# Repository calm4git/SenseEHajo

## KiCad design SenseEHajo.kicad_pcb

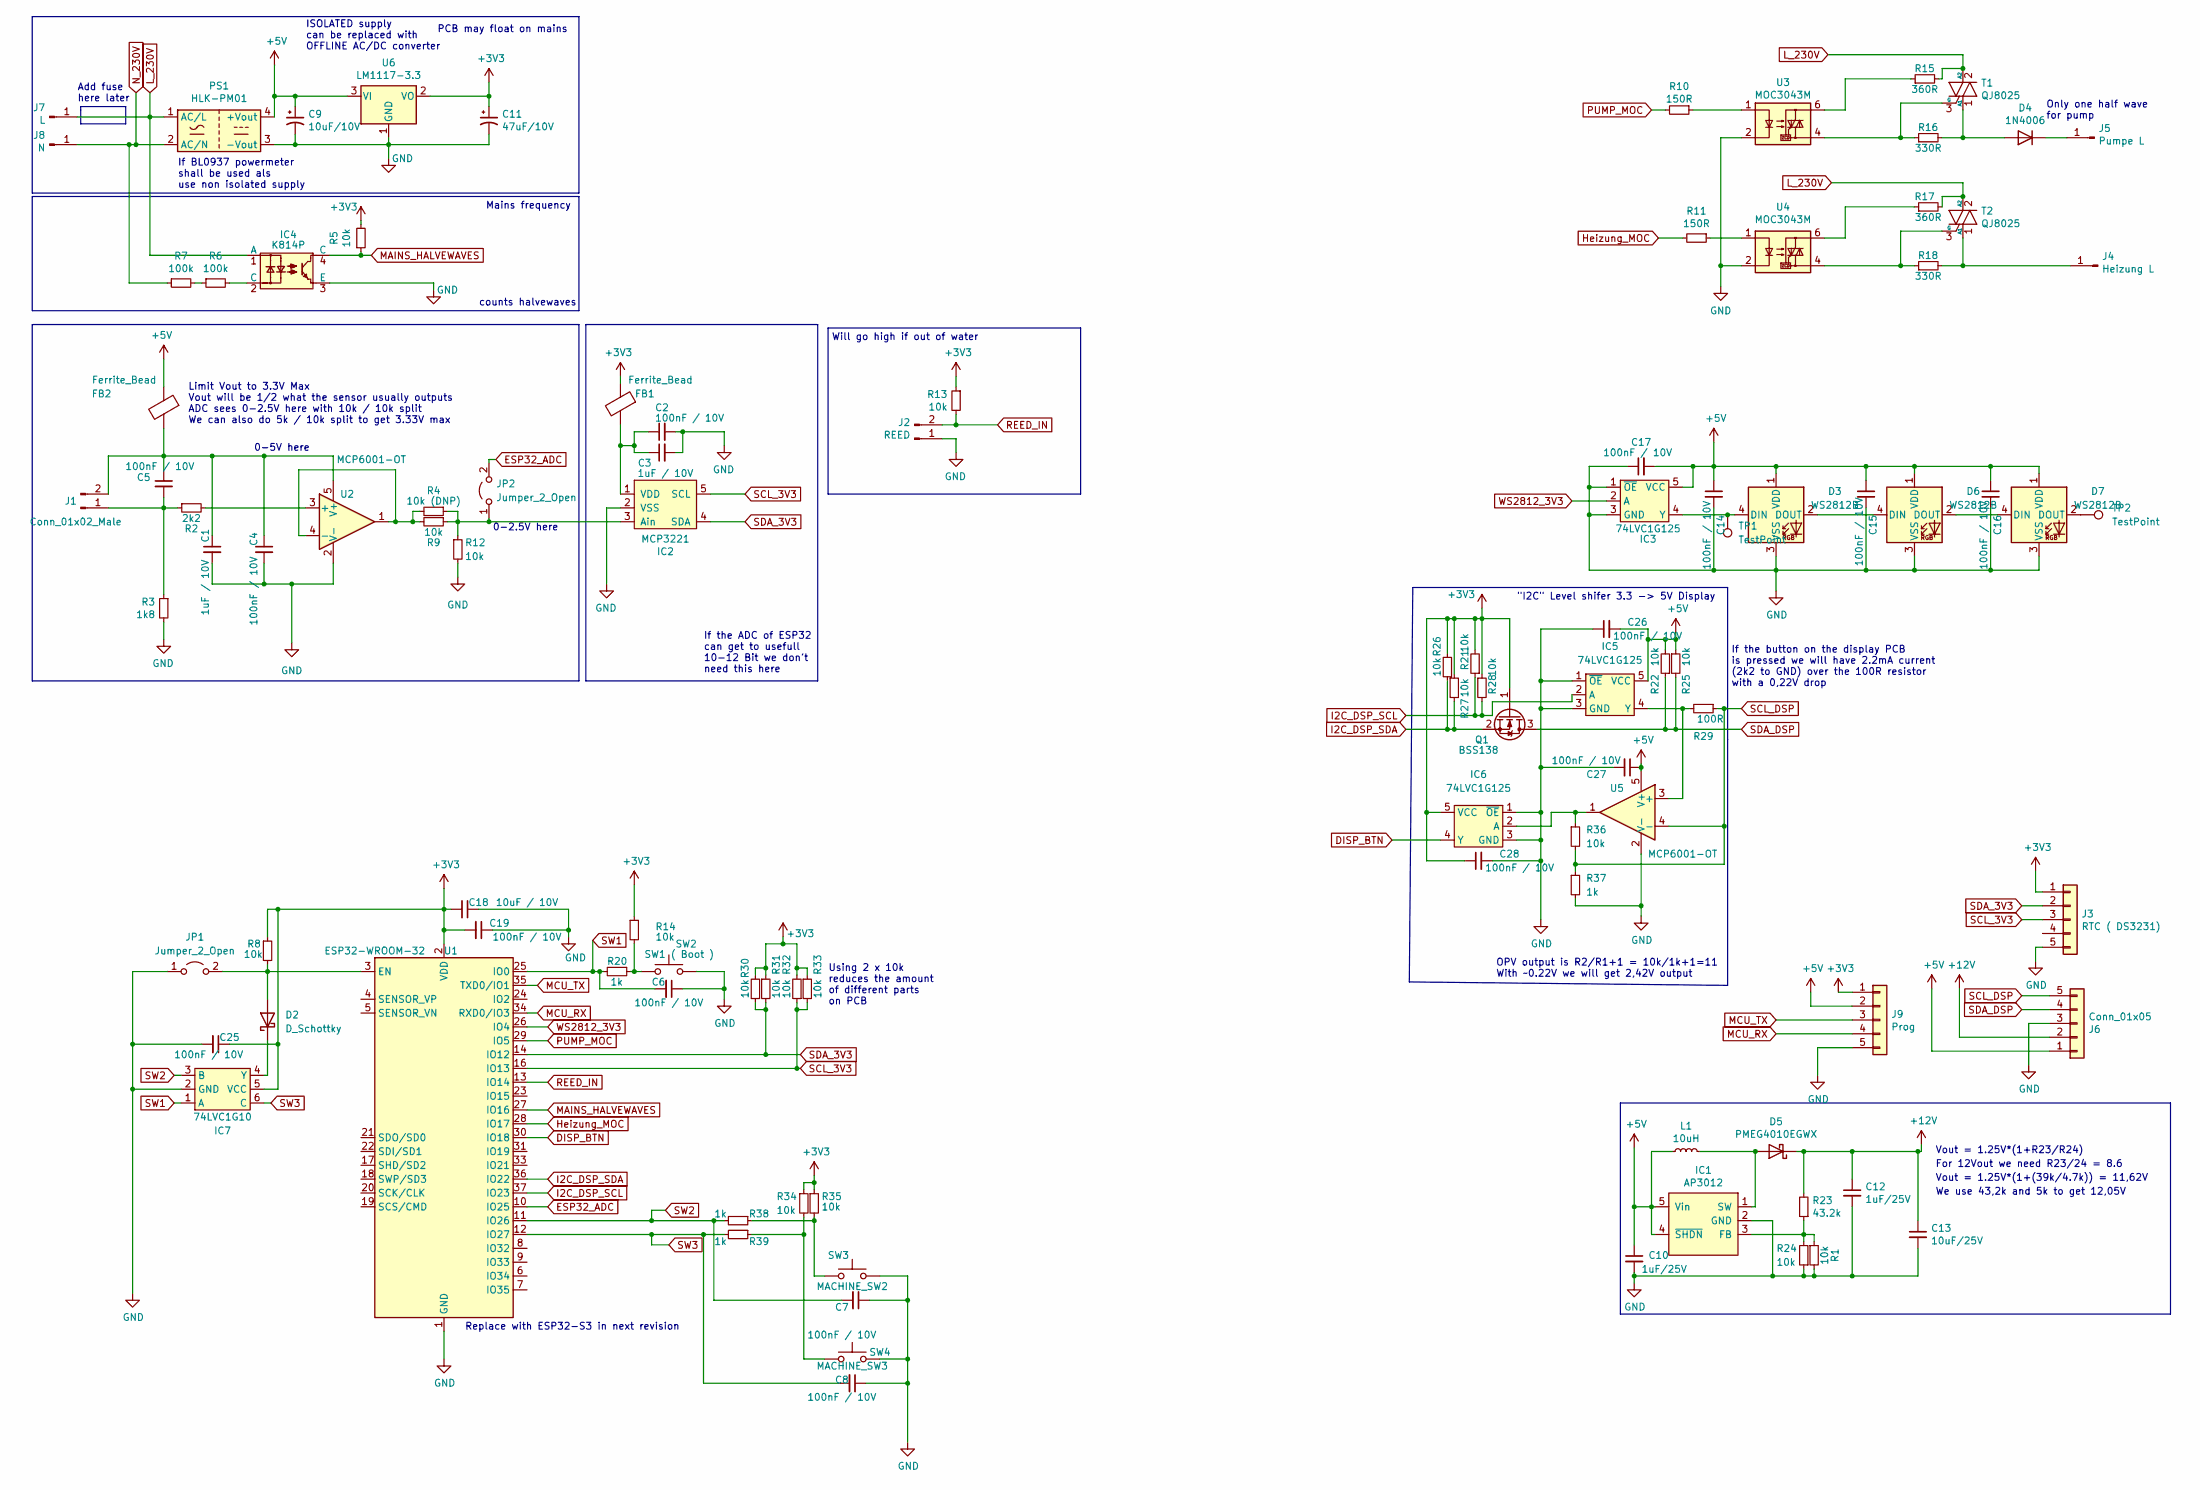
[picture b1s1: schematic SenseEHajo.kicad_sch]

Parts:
C1, C3: 1uF / 10V; C_0805_2012Metric_Pad1.18x1.45mm_HandSolder
C2, C4, C5, C6, C7, C8, C14, C15, C16, C17, C19, C25, C26, C27, C28: 100nF / 10V; C_0805_2012Metric_Pad1.18x1.45mm_HandSolder
C9: 10uF/10V; CP_Elec_4x4.5
C10, C12: 1uF/25V; C_0805_2012Metric_Pad1.18x1.45mm_HandSolder
C11: 47uF/10V; CP_Elec_5x5.3
C13: 10uF/25V; C_0805_2012Metric_Pad1.18x1.45mm_HandSolder
C18: 10uF / 10V; C_0805_2012Metric_Pad1.18x1.45mm_HandSolder
D2: D_Schottky; D_SOD-523
D3, D6, D7: WS2812B; LED_WS2812B_PLCC4_5.0x5.0mm_P3.2mm
D4: 1N4006; D_DO-201AD_P15.24mm_Horizontal
D5: PMEG4010EGWX; D_SOD-123
FB1, FB2: Ferrite_Bead; R_0805_2012Metric_Pad1.20x1.40mm_HandSolder
IC1: AP3012; SOT-23-5_HandSoldering
IC2: MCP3221; SOT-23-5_HandSoldering
IC3, IC5, IC6: 74LVC1G125; SC-74A
IC4: K814P; DIP-4_W7.62mm
IC7: 74LVC1G10; SOT-23-6_Handsoldering
J1: Conn_01x02_Male; PinHeader_1x02_P2.54mm_Vertical
J2: REED; PinHeader_1x02_P2.54mm_Vertical
J3: RTC ( DS3231); PinHeader_1x05_P2.54mm_Vertical
J4: Heizung L; MountingHole_2.7mm_M2.5_DIN965_Pad_TopBottom
J5: Pumpe L; MountingHole_2.7mm_M2.5_DIN965_Pad_TopBottom
J6: Conn_01x05; PinHeader_1x05_P2.54mm_Vertical
J7: L; MountingHole_2.7mm_M2.5_DIN965_Pad_TopBottom
J8: N; MountingHole_2.7mm_M2.5_DIN965_Pad_TopBottom
J9: Prog; PinHeader_1x05_P2.54mm_Vertical
JP1, JP2: Jumper_2_Open; SolderJumper-2_P1.3mm_Open_RoundedPad1.0x1.5mm
L1: 10uH; L_Wuerth_MAPI-3015
PS1: HLK-PM01; Converter_ACDC_HiLink_HLK-PMxx
Q1: BSS138; SOT-23
R1, R5, R8, R9, R12, R13, R14, R21, R22, R24, R25, R26, R27, R28, R30, R31, R32, R33, R34, R35, R36: 10k; R_0805_2012Metric_Pad1.20x1.40mm_HandSolder
R2: 2k2; R_0805_2012Metric_Pad1.20x1.40mm_HandSolder
R3: 1k8; R_0805_2012Metric_Pad1.20x1.40mm_HandSolder
R4: 10k (DNP); R_0805_2012Metric_Pad1.20x1.40mm_HandSolder
R6, R7: 100k; R_Axial_DIN0207_L6.3mm_D2.5mm_P7.62mm_Horizontal
R10, R11: 150R; R_0805_2012Metric_Pad1.20x1.40mm_HandSolder
R15, R17: 360R; R_Axial_DIN0207_L6.3mm_D2.5mm_P7.62mm_Horizontal
R16, R18: 330R; R_Axial_DIN0207_L6.3mm_D2.5mm_P7.62mm_Horizontal
R20, R37, R38, R39: 1k; R_0805_2012Metric_Pad1.20x1.40mm_HandSolder
R23: 43.2k; R_0805_2012Metric_Pad1.20x1.40mm_HandSolder
R29: 100R; R_0805_2012Metric_Pad1.20x1.40mm_HandSolder
SW2: SW1 ( Boot ); SW_PUSH_6mm
SW3: MACHINE_SW2; SW_PUSH_6mm
SW4: MACHINE_SW3; SW_PUSH_6mm
T1, T2: QJ8025; TO-263-3_TabPin2
TP1, TP2: TestPoint; TestPoint_Pad_D2.0mm
U1: ESP32-WROOM-32; ESP32-WROOM-32_HandSolder
U2, U5: MCP6001-OT; SOT-23-5
U3, U4: MOC3043M; DIP-6_W7.62mm
U6: LM1117-3.3; SOT-223-3_TabPin2

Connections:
+3V3: C11.1, C18.2, C19.2, C25.1, C28.1, FB1.1, IC6.5 (VCC), IC7.5 (VCC), J3.1, J9.1, Q1.1 (G), R5.2, R8.1, R13.1, R14.1, R21.2, R26.2, R27.1, R28.1, R30.2, R31.1, R32.2, R33.1, R34.1, R35.1, U1.2 (VDD), U6.2 (VO)
+5V: C9.1, C10.1, C14.1, C15.1, C16.1, C17.2, C26.2, C27.1, D3.1 (VDD), D6.1 (VDD), D7.1 (VDD), FB2.1, IC1.4 (~SHDN), IC1.5 (Vin), IC3.5 (VCC), IC5.5 (VCC), J6.1, J9.2, L1.1, PS1.4 (+Vout), R22.2, R25.1, U5.5 (V+), U6.3 (VI)
+12V: C12.1, C13.1, D5.1 (K), J6.2, R23.2
DISP_BTN: IC6.4 (Y), U1.30 (IO18)
ESP32_ADC: JP2.2 (B), U1.10 (IO25)
GND: C1.2, C2.2, C3.2, C4.2, C6.1, C7.1, C8.1, C9.2, C10.2, C11.2, C12.2, C13.2, C14.2, C15.2, C16.2, C17.1, C18.1, C19.1, C25.2, C26.1, C27.2, C28.2, D3.3 (VSS), D6.3 (VSS), D7.3 (VSS), IC1.2 (GND), IC2.2 (VSS), IC3.1 (~OE), IC3.3 (GND), IC4.3 (E), IC5.1 (~OE), IC5.3 (GND), IC6.1 (~OE), IC6.3 (GND), IC7.2 (GND), J2.1, J3.5, J6.3, J9.5, JP1.1 (A), PS1.3 (-Vout), R1.2, R3.2, R12.2, R24.1, R37.2, SW2.2, SW3.2, SW4.2, U1.1 (GND), U1.15 (GND), U1.38 (GND), U1.39 (GND), U2.2 (V-), U3.2, U4.2, U5.2 (V-), U6.1 (GND)
Heizung_MOC: R11.2, U1.28 (IO17)
I2C_DSP_SCL: IC5.2 (A), R21.1, R28.2, U1.37 (IO23)
I2C_DSP_SDA: Q1.2 (S), R26.1, R27.2, U1.36 (IO22)
L_230V: IC4.1 (A), J7.1, PS1.1 (AC/L), R15.2, R17.2, T1.2 (A2), T2.2 (A2)
MAINS_HALVEWAVES: IC4.4 (C), R5.1, U1.27 (IO16)
MCU_RX: J9.4, U1.34 (RXD0/IO3)
MCU_TX: J9.3, U1.35 (TXD0/IO1)
N_230V: J8.1, PS1.2 (AC/N), R7.1
unnamed: C1.1, C4.1, C5.1, FB2.2, J1.2, U2.5 (V+)
unnamed: C2.1, C3.1, FB1.2, IC2.1 (VDD)
unnamed: C5.2, J1.1, R2.1, R3.1
unnamed: D2.1 (K), IC7.4 (Y)
unnamed: D2.2 (A), JP1.2 (B), R8.2, U1.3 (EN)
unnamed: D3.2 (DOUT), D6.4 (DIN)
unnamed: D3.4 (DIN), IC3.4 (Y), TP1.1
unnamed: D4.1 (K), J5.1
unnamed: D4.2 (A), R16.2, T1.1 (A1)
unnamed: D5.2 (A), IC1.1 (SW), L1.2
unnamed: D6.2 (DOUT), D7.4 (DIN)
unnamed: D7.2 (DOUT), TP2.1
unnamed: IC1.3 (FB), R1.1, R23.1, R24.2
unnamed: IC2.3 (Ain), JP2.1 (A), R4.1, R9.1, R12.1
unnamed: IC4.2 (C), R6.2
unnamed: IC5.4 (Y), R29.2, U5.3 (+)
unnamed: IC6.2 (A), R36.1, U5.1
unnamed: J4.1, R18.2, T2.1 (A1)
unnamed: R2.2, U2.3 (+)
unnamed: R4.2, R9.2, U2.1, U2.4 (-)
unnamed: R6.1, R7.2
unnamed: R10.1, U3.1
unnamed: R11.1, U4.1
unnamed: R14.2, R20.1, SW2.1
unnamed: R15.1, U3.6
unnamed: R16.1, T1.3 (G), U3.4
unnamed: R17.1, U4.6
unnamed: R18.1, T2.3 (G), U4.4
unnamed: R34.2, R39.1, SW4.1
unnamed: R35.2, R38.1, SW3.1
PUMP_MOC: R10.2, U1.29 (IO5)
REED_IN: J2.2, R13.2, U1.13 (IO14)
SCL_3V3: IC2.5 (SCL), J3.3, R32.1, R33.2, U1.16 (IO13)
SCL_DSP: J6.5, R29.1, R36.2, R37.1, U5.4 (-)
SDA_3V3: IC2.4 (SDA), J3.2, R30.1, R31.2, U1.14 (IO12)
SDA_DSP: J6.4, Q1.3 (D), R22.1, R25.2
SW1: C6.2, IC7.1 (A), R20.2, U1.25 (IO0)
SW2: C7.2, IC7.3 (B), R38.2, U1.11 (IO26)
SW3: C8.2, IC7.6 (C), R39.2, U1.12 (IO27)
WS2812_3V3: IC3.2 (A), U1.26 (IO4)

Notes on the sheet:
Limit Vout to 3.3V Max Vout will be 1/2 what the sensor usually outputs ADC sees 0-2.5V here with 10k / 10k split We can also do 5k / 10k split to get 3.33V max
Mains frequency
If BL0937 powermeter shall be used als use non isolated supply
Vout = 1.25V*(1+(39k/4.7k)) = 11,62V
If the ADC of ESP32 can get to usefull 10-12 Bit we don't need this here
"I2C" Level shifer 3.3 -> 5V Display
If the button on the display PCB is pressed we will have 2.2mA current (2k2 to GND) over the 100R resistor with a 0,22V drop
Only one half wave for pump
counts halvewaves
Add fuse here later
For 12Vout we need R23/24 = 8.6
OPV output is R2/R1+1 = 10k/1k+1=11 With ~0.22V we will get 2,42V output
0-2.5V here
Replace with ESP32-S3 in next revision
0-5V here
Using 2 x 10k reduces the amount of different parts on PCB
Vout = 1.25V*(1+R23/R24)
Will go high if out of water
PCB may float on mains
ISOLATED supply can be replaced with OFFLINE AC/DC converter
We use 43,2k and 5k to get 12,05V

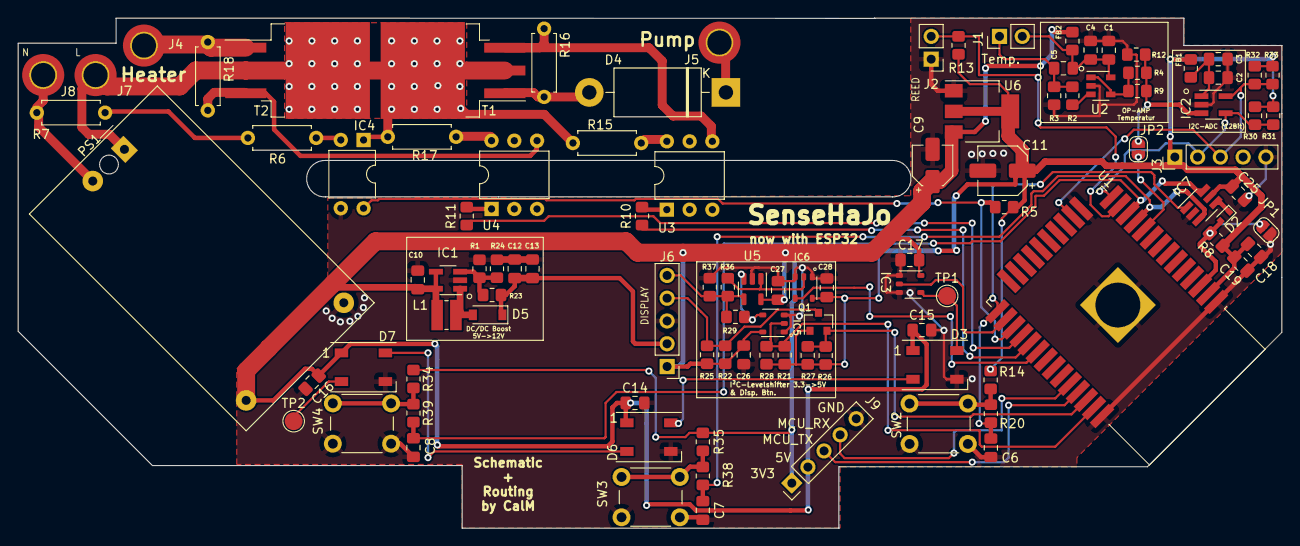
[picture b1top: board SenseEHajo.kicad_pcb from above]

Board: 2 copper layers, 141.0 x 56.9 mm, 103 parts (0 on the bottom side), 54 nets.

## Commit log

2019-12-27 Inital Commit
    will not work at all
2019-12-27 CleanUp
    Small Cleanup on the PCB
2019-12-28 Added Netfrequency Detection
    This will detect the Netfrequency on IO25 of the ESP32. This is usefull to determine the amount of water pumped to the cup
2020-01-03 Small modifications
    The AC/DC supply is operating on the edge of it's limits now
2023-06-25 Version3
    Ordered Proto for Version 3
2023-09-09 Fix Display BTP senese for press
2023-10-05 MK III
2023-10-08 Add SenseEHajo-backups to ignore
